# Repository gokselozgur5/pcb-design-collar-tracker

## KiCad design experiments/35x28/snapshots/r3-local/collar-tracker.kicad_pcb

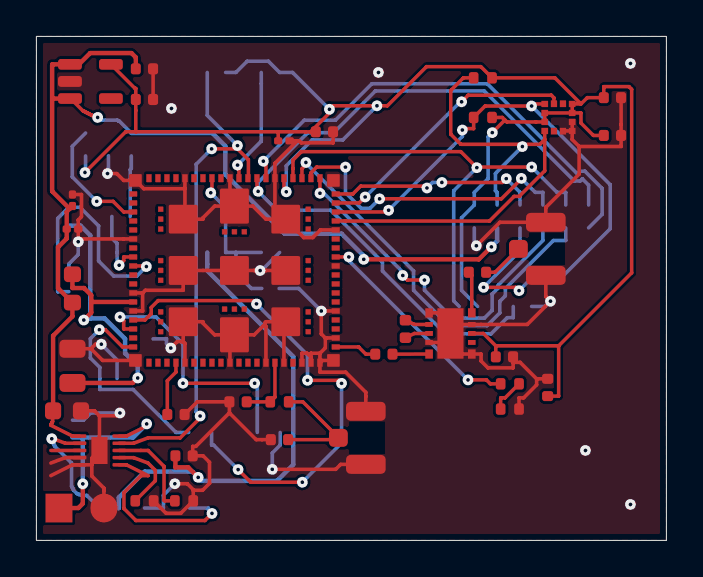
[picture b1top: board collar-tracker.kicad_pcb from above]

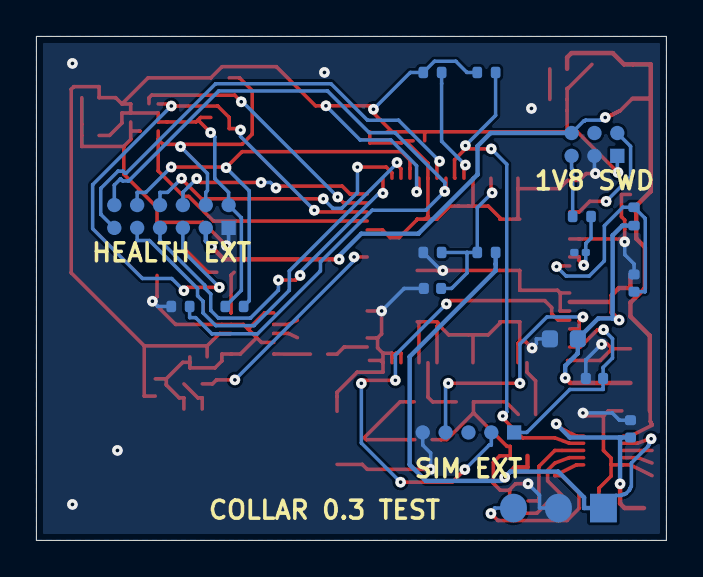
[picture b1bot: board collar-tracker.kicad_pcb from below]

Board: 4 copper layers, 35.0 x 28.0 mm, 53 parts (18 on the bottom side), 42 nets.

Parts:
C1, C2: 1uF /10V; C_0201_0603Metric
C3: 47uF /10V; C_0805_2012Metric
C4, C18: 10uF /10V; C_0603_1608Metric
C5, C8: 100nF; C_0201_0603Metric
C6, C7: 4.7uF; C_0402_1005Metric
C9, C10, C15, C23, C24: 100nF; C_0402_1005Metric
C11, C12: DNP / tune; C_0402_1005Metric
C13, C14: 39pF RF; C_0402_1005Metric
C16, C20, C21: 1uF; C_0402_1005Metric
C17, C19: 1uF /10V; C_0402_1005Metric
C22: 10nF; C_0402_1005Metric
FB1: 22R @100MHz; L_0603_1608Metric
J1: LTE antenna / 50R; U.FL_Hirose_U.FL-R-SMT-1_Vertical
J2: GNSS antenna / passive; U.FL_Hirose_U.FL-R-SMT-1_Vertical
J3: 5V charging input; Solder_1x02_P2.5mm
J4: Protected cell + NTC; Solder_1x03_P2.5mm
J5: DIGITAL health sensor interface; Contact_2x06_P1.27mm
J6: eSIM interface / SKU TBD; Contact_1x05_P1.27mm
J7: SWD / debug; Contact_2x03_P1.27mm
L1: 9.1nH; L_0402_1005Metric
R1, R8, R9: 10k; R_0402_1005Metric
R2, R4: 1k; R_0402_1005Metric
R3: 0R / tune; R_0402_1005Metric
R5, R14, R15: 100k; R_0402_1005Metric
R6: 18k /1%; R_0402_1005Metric
R7: 3k /1%; R_0402_1005Metric
R10: 2M; R_0402_1005Metric
R11: 1M; R_0402_1005Metric
R12, R13: 4.7k; R_0402_1005Metric
U1: nRF9151-LACA; LGA_9151_12.1x11.1mm
U2: SKY65943-11; SKY65943_DK10171
U3: BQ25185DLHR; Texas_DLH0010A_WSON-10-1EP_2.2x2mm_P0.4mm_EP0.9x1.5mm
U4: TPS7A0218PDBVR; SOT-23-5
U5: LIS2DW12TR; LGA-12_2x2mm_P0.5mm

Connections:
/ACC_INT: U1.58, U5.12
/AMP_IN: L1.2, U2.8
/BAT_ADC: C22.1, R10.2, R11.1, U1.73
/BAT_NTC: J4.3, U3.6
/CHG_FAULT: R9.1, U1.70, U3.3
/CHG_STAT: R8.1, U1.69, U3.9
/COEX0: R4.1, U1.52
/DEBUG_RESET: J7.5, R2.2
/DEC0: C7.1, U1.24
/FILT_OUT: L1.1, U2.7
/GND: C1.2, C2.2, C3.2, C4.2, C5.2, C6.2, C7.2, C8.2, C9.2, C10.2, C11.2, C12.2, C15.2, C16.2, C17.2, C18.2, C19.2, C20.2, C21.2, C22.2, C23.2, C24.2, J1.2, J2.2, J3.2, J4.2, J5.1, J6.5, J7.3, R5.2, R6.2, R7.2, R11.2, R15.2, U1.1, U1.7, U1.13, U1.15, U1.20, U1.25, U1.30, U1.34, U1.36, U1.38, U1.39, U1.40, U1.41, U1.43, U1.46, U1.51, U1.55, U1.60, U1.66, U1.71, U1.76, U1.105, U1.106, U1.107, U1.108, U1.109, U1.110, U1.111, U1.112, U1.113, U2.1, U2.4, U2.6, U2.9, U2.11, U3.4, U3.5, U3.11, U4.2, U5.6, U5.7, U5.8
/GNSS_ANT: C14.1, J2.1
/GNSS_FEM_IN: C14.2, U2.5
/GNSS_FEM_OUT: C13.1, U2.10
/GNSS_LNA_EN: R4.2, R5.1, U2.2
/GPS_RF: C13.2, U1.42
/HEALTH_CS: J5.10, R14.1, U1.64
/HEALTH_EN: J5.12, R15.1, U1.68
/HEALTH_INT: J5.6, U1.59
/HEALTH_RESET: J5.11, U1.67
/I2C_SCL: J5.5, R13.1, U1.57, U5.1
/I2C_SDA: J5.4, R12.1, U1.56, U5.4
/ILIM_VSET: R6.1, U3.7
/ISET: R7.1, U3.8
/LTE_ANT: C12.1, J1.1, R3.2
/LTE_RF: C11.1, R3.1, U1.35
/NRF_ENABLE: C9.1, R1.2, U1.10
/NRF_RESET: C8.1, R2.1, U1.9
/SIM_1V8: C10.1, J6.1, U1.19
/SIM_CLK: J6.3, U1.18
/SIM_IO: J6.4, U1.17
/SIM_RST: J6.2, U1.16
/SPI_MISO: J5.9, U1.63
/SPI_MOSI: J5.8, U1.62
/SPI_SCK: J5.7, U1.61
/SWDCLK: J7.4, U1.3
/SWDIO: J7.2, U1.4
/VBAT: C19.1, J4.1, R10.1, U3.2
/VDD_NRF: C3.1, C4.1, FB1.2, R1.1, U1.14
/VIN_5V: C17.1, J3.1, U3.10
/VIO_1V8: C5.1, C6.1, C15.1, C16.1, C21.1, C23.1, C24.1, J5.2, J7.1, R8.2, R9.2, R12.2, R13.2, R14.2, U1.65, U2.3, U4.5, U5.2, U5.3, U5.9, U5.10
/VSYS: C1.1, C2.1, C18.1, C20.1, FB1.1, J5.3, J7.6, U3.1, U4.1, U4.3
